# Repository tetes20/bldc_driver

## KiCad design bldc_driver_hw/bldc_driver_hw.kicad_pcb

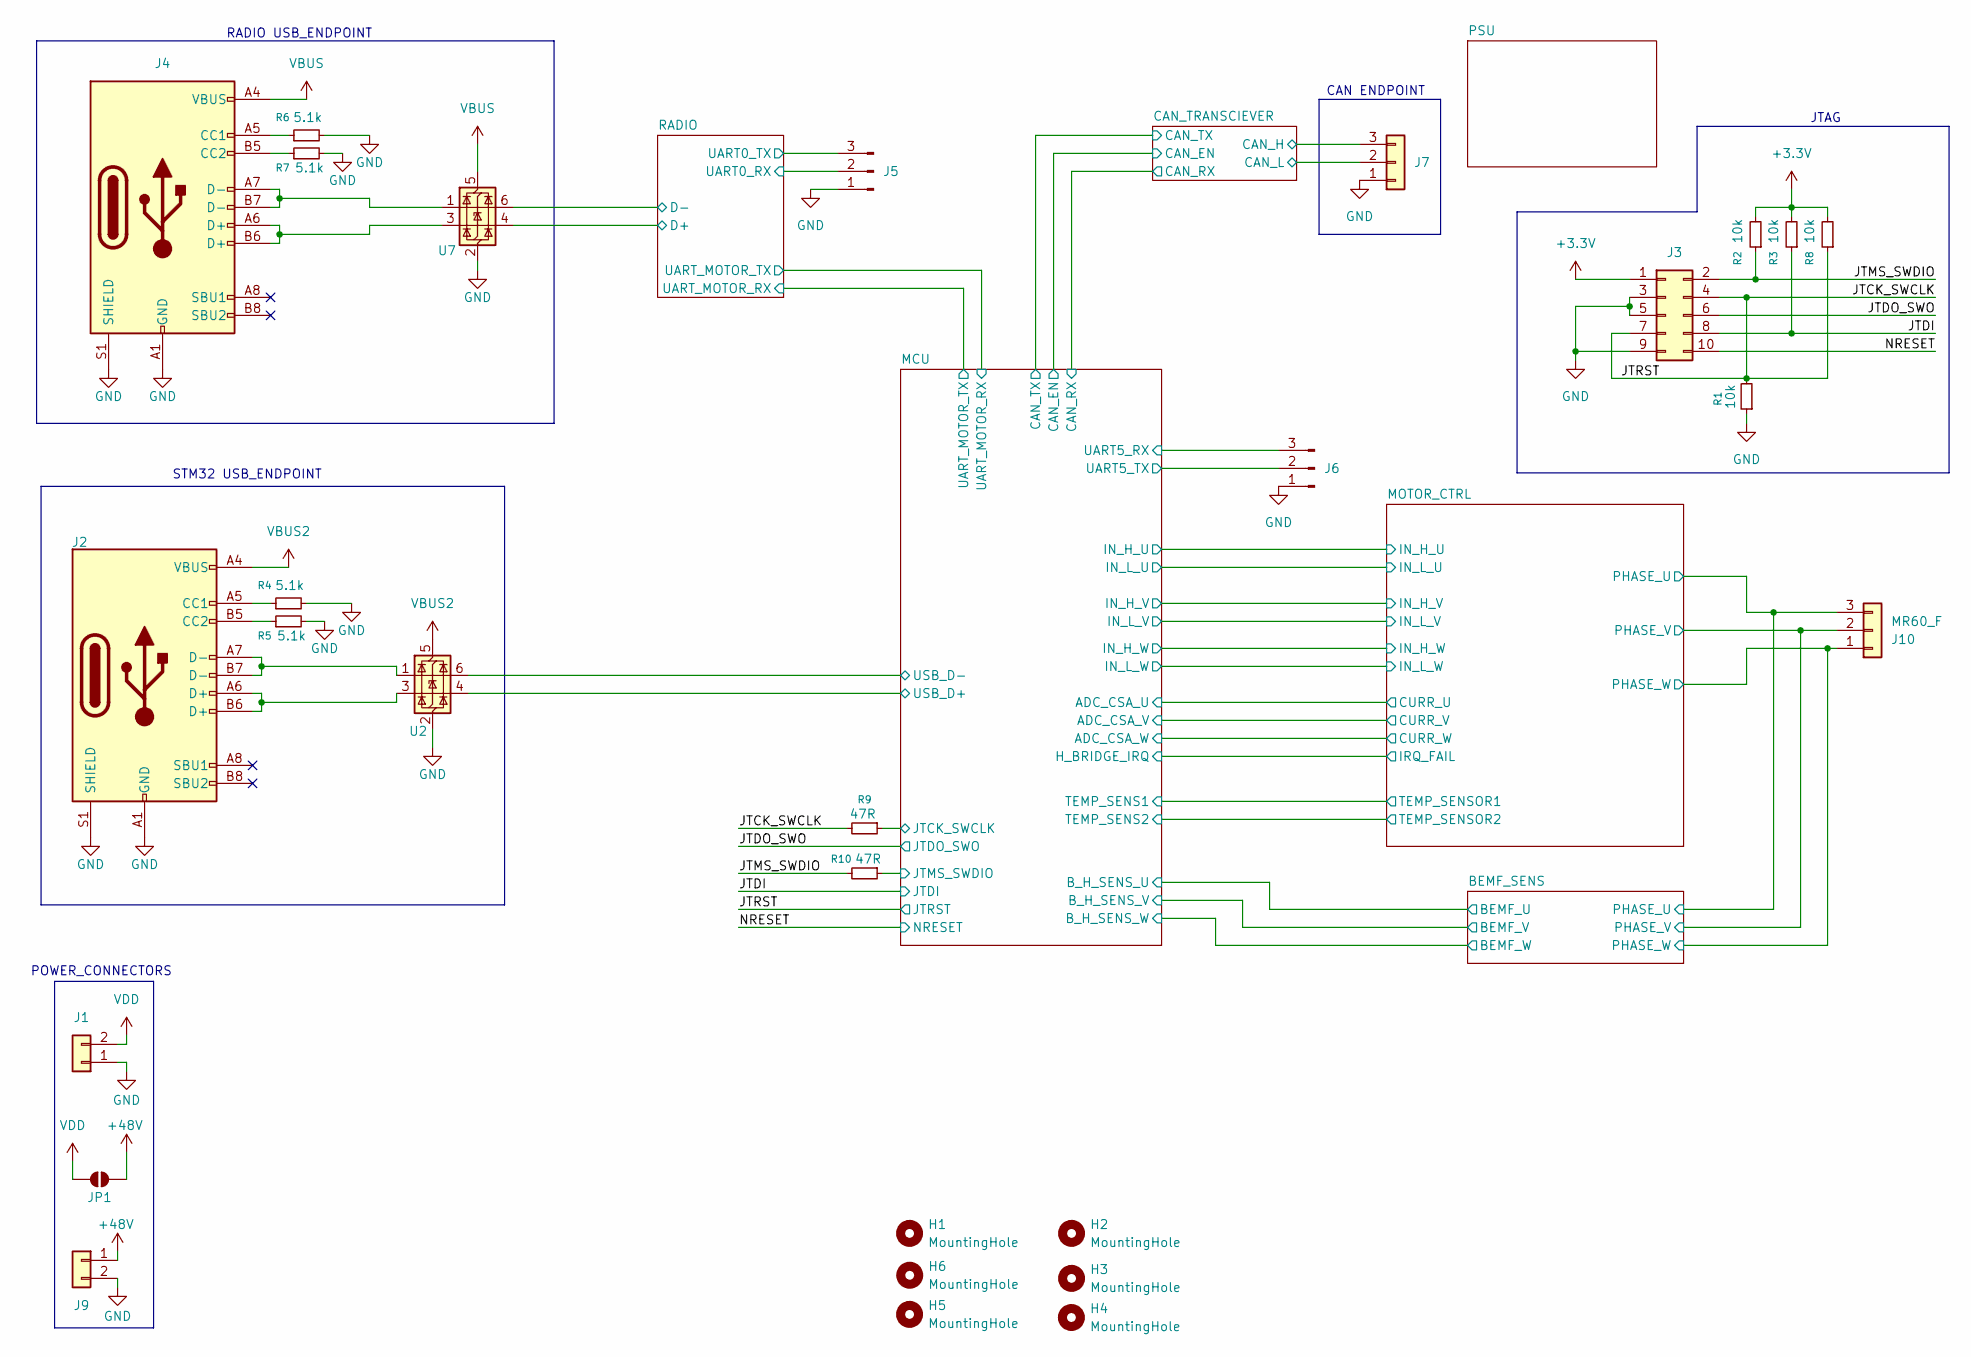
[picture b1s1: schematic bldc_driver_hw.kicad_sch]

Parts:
H1, H2, H3, H4, H5, H6: MountingHole; MountingHole_3.2mm_M3
J1: Conn_01x02; TerminalBlock_4Ucon_1x02_P3.50mm_Horizontal
J2, J4: USB_C_Receptacle_USB2.0_16P; USB_C_Receptacle_GCT_USB4105-xx-A_16P_TopMnt_Horizontal
J3: JTAG_CONN; PinHeader_2x05_P2.54mm_Vertical
J5, J6: Conn_01x03_Pin; PinHeader_1x03_P2.54mm_Vertical
J7: Conn_01x03; TerminalBlock_4Ucon_1x03_P3.50mm_Horizontal
J9: Conn_01x02; AMASS_XT60-F_1x02_P7.20mm_Vertical
J10: MR60_F; PhoenixContact_GMSTBVA_2,5_3-G_1x03_P7.50mm_Vertical
JP1: SolderJumper_2_Open; SolderJumper-2_P1.3mm_Open_Pad1.0x1.5mm
R1, R2, R3, R8: 10k; R_0603_1608Metric; LCSC C25804
R4, R5, R6, R7: 5.1k; R_0603_1608Metric; LCSC C23186
R9, R10: 47R; R_0603_1608Metric; LCSC C23182
U2, U7: USBLC6-2SC6; SOT-23-6

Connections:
+3.3V: J3.1, R2.2, R3.2, R8.2; also elsewhere on the board
+48V: J9.1, JP1.1 (A); also elsewhere on the board
/BEMF_SENS/PHASE_U: J10.3; also elsewhere on the board
/BEMF_SENS/PHASE_V: J10.2; also elsewhere on the board
/BEMF_SENS/PHASE_W: J10.1; also elsewhere on the board
/CAN_TRANSCIEVER/CAN_H: J7.3; also elsewhere on the board
/CAN_TRANSCIEVER/CAN_L: J7.2; also elsewhere on the board
/JTCK_SWCLK: J3.4, J3.7, R1.2, R8.1, R9.2; also elsewhere on the board
/JTDI: J3.8, R3.1; also elsewhere on the board
/JTDO_SWO: J3.6; also elsewhere on the board
/JTMS_SWDIO: J3.2, R2.1, R10.2
/MCU/JTCK_SWCLK: R9.1; also elsewhere on the board
/MCU/JTMS_SWDIO: R10.1; also elsewhere on the board
/MCU/UART5_RX: J6.3; also elsewhere on the board
/MCU/UART5_TX: J6.2; also elsewhere on the board
/MCU/USB_D+: U2.4 (I/O2); also elsewhere on the board
/MCU/USB_D-: U2.6 (I/O1); also elsewhere on the board
/NRESET: J3.10; also elsewhere on the board
/RADIO/D+: U7.4 (I/O2); also elsewhere on the board
/RADIO/D-: U7.6 (I/O1); also elsewhere on the board
/RADIO/UART0_RX: J5.2; also elsewhere on the board
/RADIO/UART0_TX: J5.3; also elsewhere on the board
GND: J1.1, J2.A1 (GND), J2.A12 (GND), J2.B1 (GND), J2.B12 (GND), J2.S1 (SHIELD), J3.3, J3.5, J3.9, J4.A1 (GND), J4.A12 (GND), J4.B1 (GND), J4.B12 (GND), J4.S1 (SHIELD), J5.1, J6.1, J7.1, J9.2, R1.1, R4.2, R5.2, R6.2, R7.2, U2.2 (GND), U7.2 (GND); also elsewhere on the board
unnamed: J2.A5 (CC1), R4.1
unnamed: J2.B5 (CC2), R5.1
unnamed: J2.A6 (D+), J2.B6 (D+), U2.3 (I/O2)
unnamed: J2.A7 (D-), J2.B7 (D-), U2.1 (I/O1)
unnamed: J4.A5 (CC1), R6.1
unnamed: J4.B5 (CC2), R7.1
unnamed: J4.A6 (D+), J4.B6 (D+), U7.3 (I/O2)
unnamed: J4.A7 (D-), J4.B7 (D-), U7.1 (I/O1)
VBUS: J4.A4 (VBUS), J4.A9 (VBUS), J4.B4 (VBUS), J4.B9 (VBUS), U7.5 (VBUS); also elsewhere on the board
VBUS2: J2.A4 (VBUS), J2.A9 (VBUS), J2.B4 (VBUS), J2.B9 (VBUS), U2.5 (VBUS); also elsewhere on the board
VDD: J1.2, JP1.2 (B); also elsewhere on the board

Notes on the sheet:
STM32 USB_ENDPOINT
JTAG
RADIO USB_ENDPOINT
CAN ENDPOINT
POWER_CONNECTORS

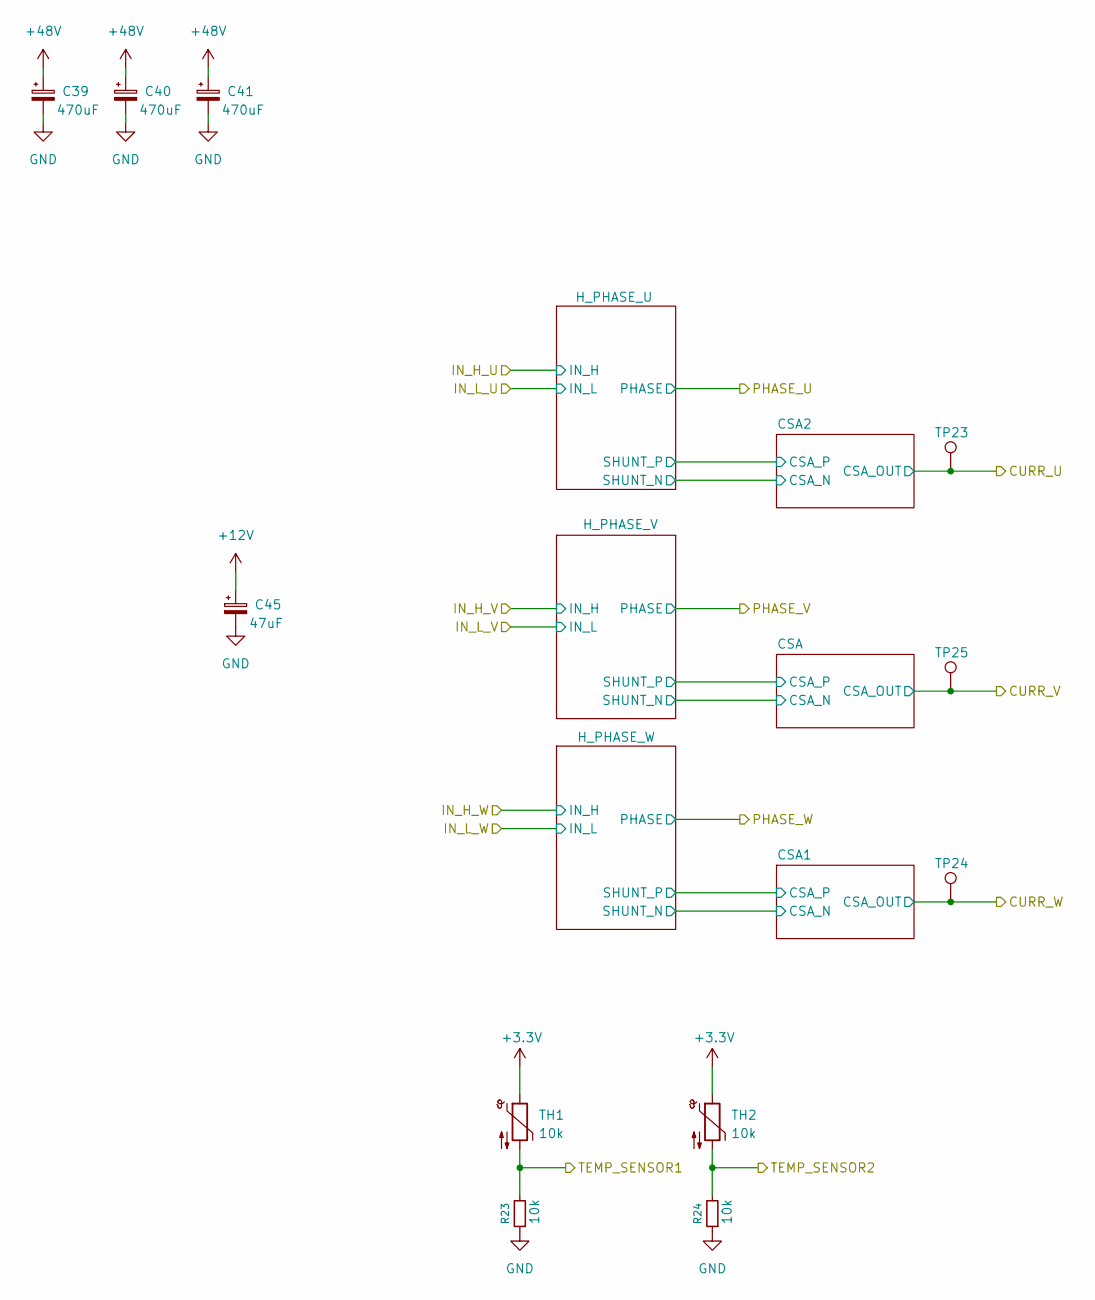
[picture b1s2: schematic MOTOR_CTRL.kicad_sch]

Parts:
C39, C40, C41: 470uF; CP_Radial_D16.0mm_P7.50mm
C45: 47uF; CP_Elec_6.3x5.4
R23, R24: 10k; R_0603_1608Metric; LCSC C25804
TH1, TH2: 10k; R_0603_1608Metric
TP23, TP24, TP25: TestPoint; TestPoint_Pad_D2.0mm

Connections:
+3.3V: TH1.1, TH2.1; also elsewhere on the board
+12V: C45.1; also elsewhere on the board
+48V: C39.1, C40.1, C41.1; also elsewhere on the board
/MCU/ADC_CSA_U: TP23.1; also elsewhere on the board
/MCU/ADC_CSA_V: TP25.1; also elsewhere on the board
/MCU/ADC_CSA_W: TP24.1; also elsewhere on the board
/MCU/TEMP_SENS1: R23.2, TH1.2; also elsewhere on the board
/MCU/TEMP_SENS2: R24.2, TH2.2; also elsewhere on the board
GND: C39.2, C40.2, C41.2, C45.2, R23.1, R24.1; also elsewhere on the board

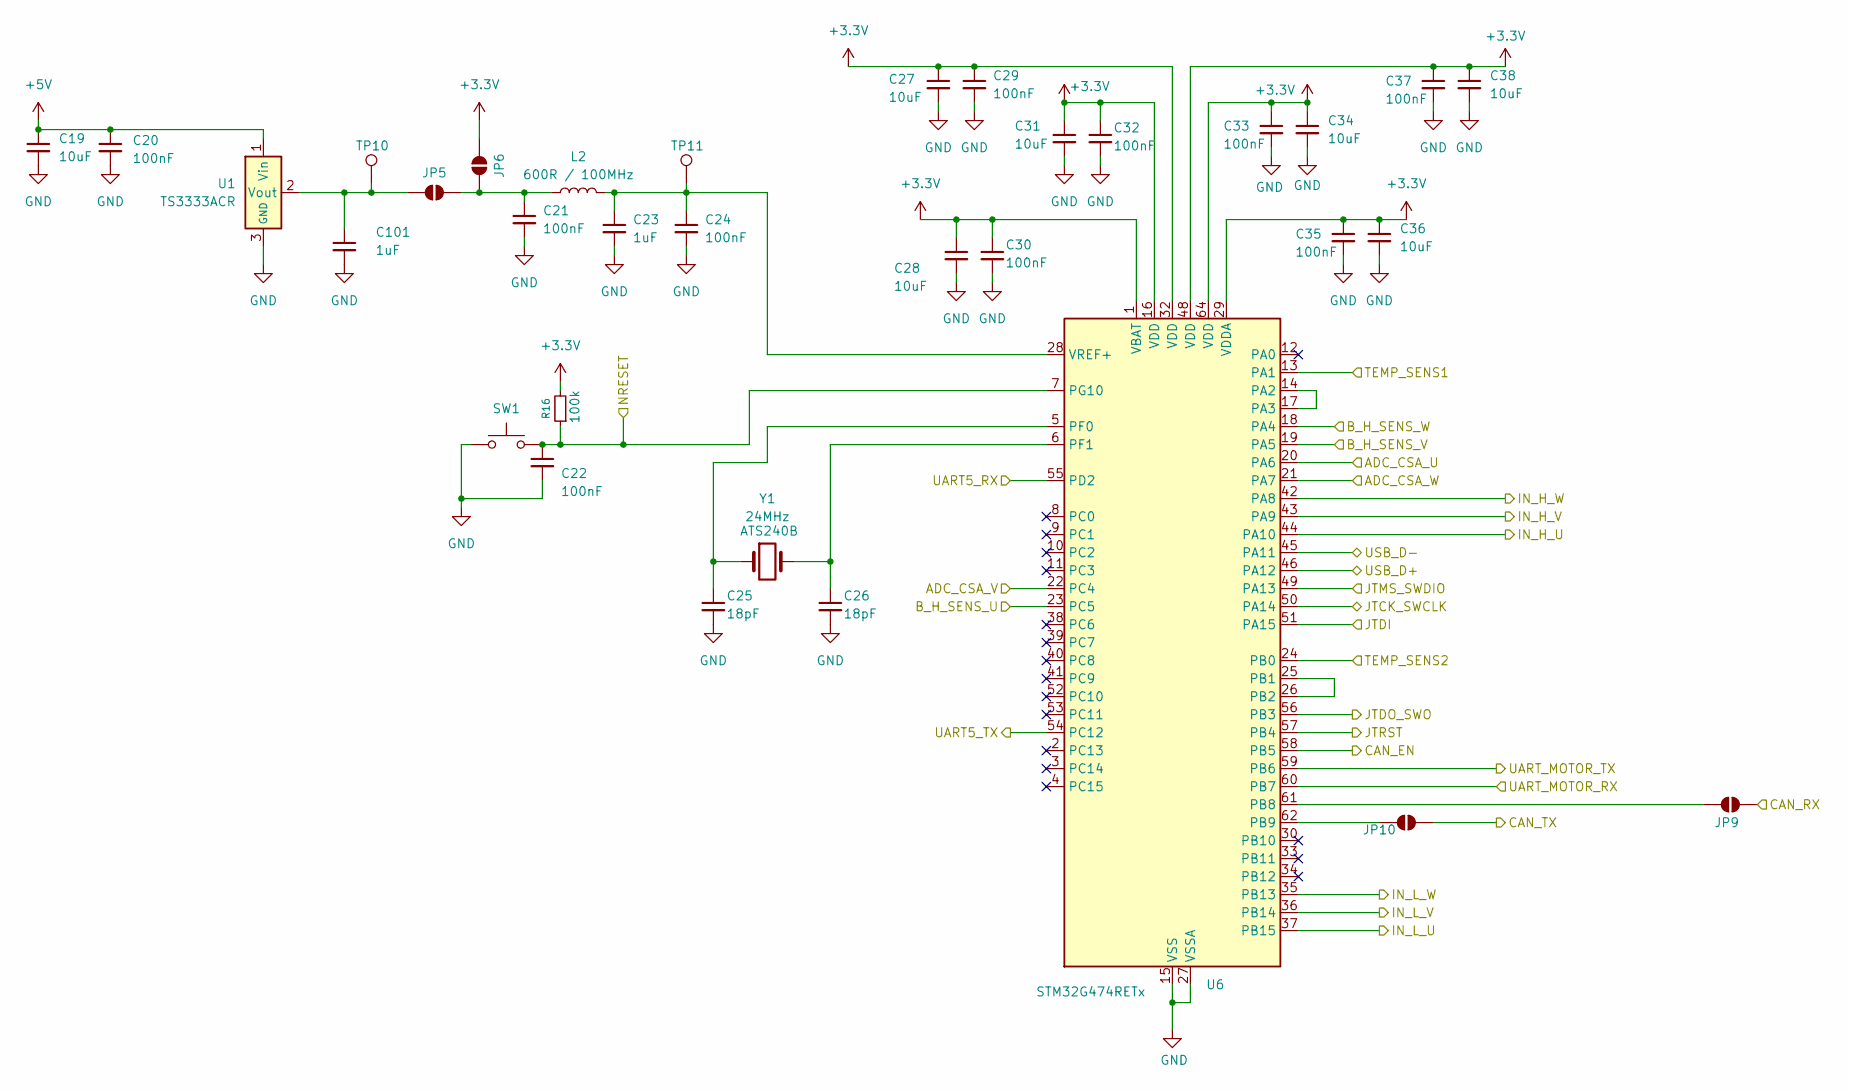
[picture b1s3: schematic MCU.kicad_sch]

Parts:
C19, C27, C28, C31, C34, C36, C38: 10uF; C_0603_1608Metric; LCSC C96446
C20, C21, C22, C24, C29, C30, C32, C33, C35, C37: 100nF; C_0603_1608Metric; LCSC C14663
C23, C101: 1uF; C_0603_1608Metric; LCSC C15849
C25, C26: 18pF; C_0603_1608Metric; LCSC C1647
JP5, JP6, JP9, JP10: SolderJumper_2_Open; SolderJumper-2_P1.3mm_Open_RoundedPad1.0x1.5mm
L2: 600R / 100MHz; R_1206_3216Metric
R16: 100k; R_0603_1608Metric; LCSC C25803
SW1: SW_Push; SW_SPST_TL3342; LCSC C318884
TP10, TP11: TestPoint; TestPoint_Pad_D2.0mm
U1: TS3333ACR; SOT-23-3
U6: STM32G474RETx; LQFP-64_10x10mm_P0.5mm
Y1: 24MHz; Crystal_HC49-U_Vertical

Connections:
+3.3V: C27.1, C28.1, C29.1, C30.1, C31.1, C32.1, C33.1, C34.1, C35.1, C36.1, C37.1, C38.1, JP6.1 (A), R16.2, U6.1 (VBAT), U6.16 (VDD), U6.29 (VDDA), U6.32 (VDD), U6.48 (VDD), U6.64 (VDD); also elsewhere on the board
+5V: C19.1, C20.1, U1.1 (Vin); also elsewhere on the board
/BEMF_SENS/BEMF_U: U6.23 (PC5); also elsewhere on the board
/BEMF_SENS/BEMF_V: U6.19 (PA5); also elsewhere on the board
/BEMF_SENS/BEMF_W: U6.18 (PA4); also elsewhere on the board
/CAN_TRANSCIEVER/CAN_EN: U6.58 (PB5); also elsewhere on the board
/CAN_TRANSCIEVER/CAN_RX: JP9.2 (B); also elsewhere on the board
/CAN_TRANSCIEVER/CAN_TX: JP10.2 (B); also elsewhere on the board
/JTCK_SWCLK: U6.57 (PB4); also elsewhere on the board
/JTDI: U6.51 (PA15); also elsewhere on the board
/JTDO_SWO: U6.56 (PB3); also elsewhere on the board
/MCU/ADC_CSA_U: U6.20 (PA6); also elsewhere on the board
/MCU/ADC_CSA_V: U6.22 (PC4); also elsewhere on the board
/MCU/ADC_CSA_W: U6.21 (PA7); also elsewhere on the board
/MCU/IN_H_U: U6.44 (PA10); also elsewhere on the board
/MCU/IN_H_V: U6.43 (PA9); also elsewhere on the board
/MCU/IN_H_W: U6.42 (PA8); also elsewhere on the board
/MCU/IN_L_U: U6.37 (PB15); also elsewhere on the board
/MCU/IN_L_V: U6.36 (PB14); also elsewhere on the board
/MCU/IN_L_W: U6.35 (PB13); also elsewhere on the board
/MCU/JTCK_SWCLK: U6.50 (PA14); also elsewhere on the board
/MCU/JTMS_SWDIO: U6.49 (PA13); also elsewhere on the board
/MCU/TEMP_SENS1: U6.13 (PA1); also elsewhere on the board
/MCU/TEMP_SENS2: U6.24 (PB0); also elsewhere on the board
/MCU/UART5_RX: U6.55 (PD2); also elsewhere on the board
/MCU/UART5_TX: U6.54 (PC12); also elsewhere on the board
/MCU/UART_MOTOR_RX: U6.60 (PB7); also elsewhere on the board
/MCU/UART_MOTOR_TX: U6.59 (PB6); also elsewhere on the board
/MCU/USB_D+: U6.46 (PA12); also elsewhere on the board
/MCU/USB_D-: U6.45 (PA11); also elsewhere on the board
/NRESET: C22.1, R16.1, SW1.2, U6.7 (PG10); also elsewhere on the board
GND: C19.2, C20.2, C21.2, C22.2, C23.2, C24.2, C25.2, C26.2, C27.2, C28.2, C29.2, C30.2, C31.2, C32.2, C33.2, C34.2, C35.2, C36.2, C37.2, C38.2, C101.2, SW1.1, U1.3 (GND), U6.15 (VSS), U6.27 (VSSA), U6.31 (VSS), U6.47 (VSS), U6.63 (VSS); also elsewhere on the board
unnamed: C101.1, JP5.1 (A), TP10.1, U1.2 (Vout)
unnamed: C21.1, JP5.2 (B), JP6.2 (B), L2.1
unnamed: JP9.1 (A), U6.61 (PB8)
unnamed: JP10.1 (A), U6.62 (PB9)
unnamed: U6.14 (PA2), U6.17 (PA3)
unnamed: U6.25 (PB1), U6.26 (PB2)
unnamed: C25.1, U6.5 (PF0), Y1.1
unnamed: C26.1, U6.6 (PF1), Y1.2
unnamed: C23.1, C24.1, L2.2, TP11.1, U6.28 (VREF+)

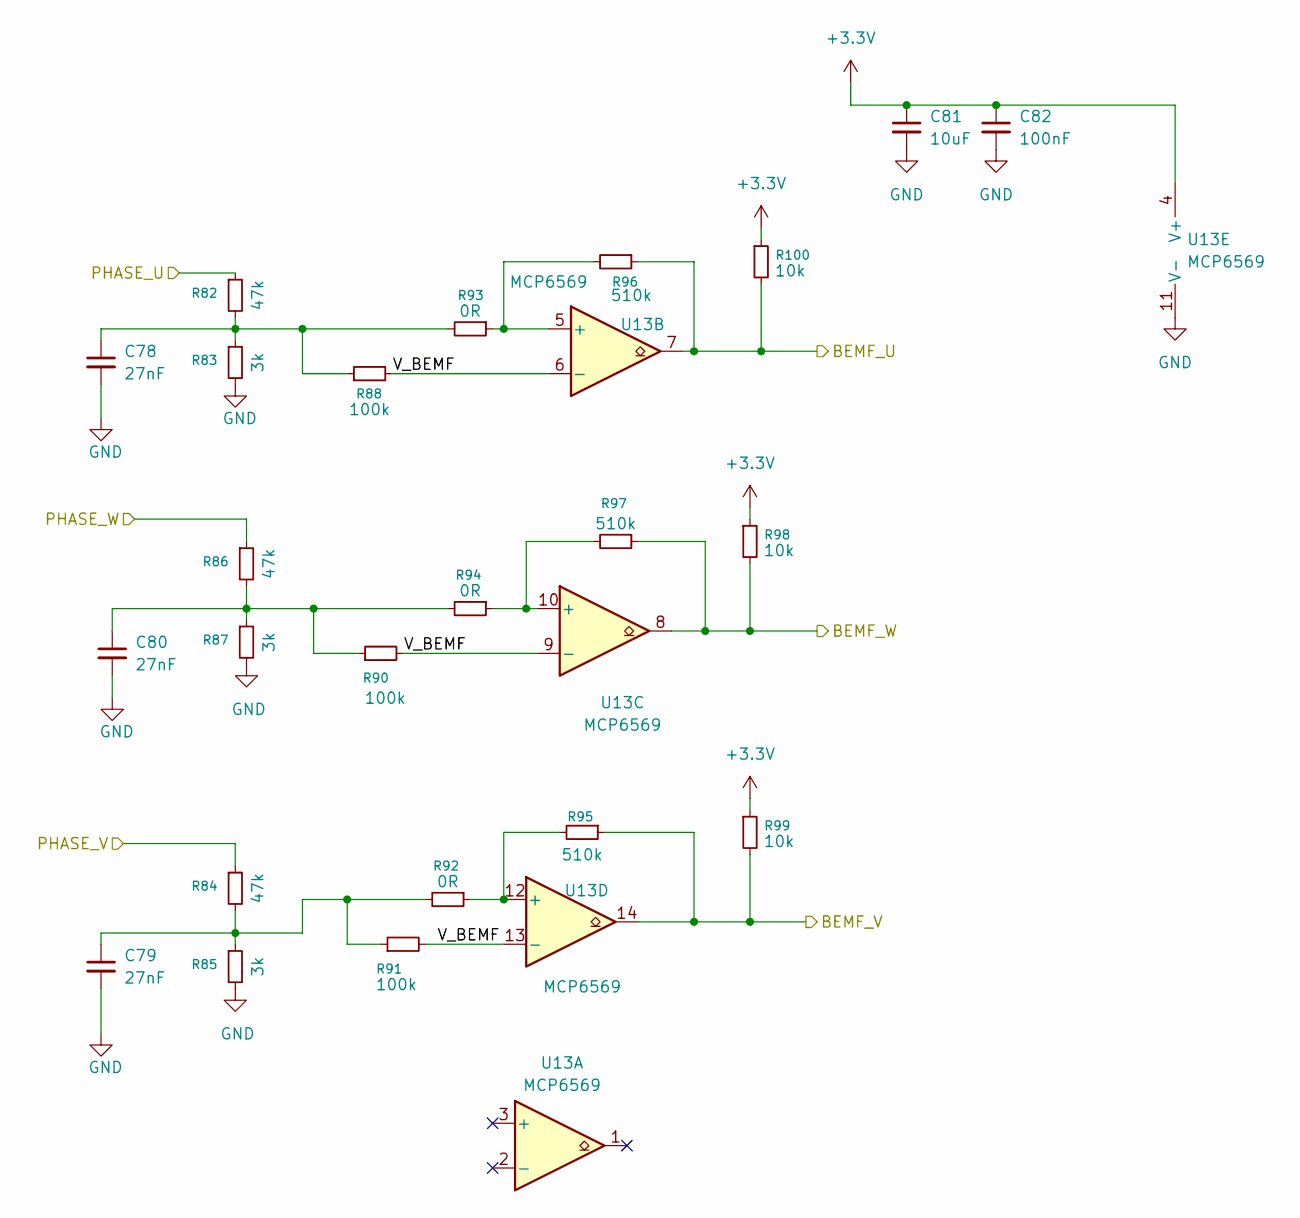
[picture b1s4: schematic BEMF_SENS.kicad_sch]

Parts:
C78, C79, C80: 27nF; C_0603_1608Metric
C81: 10uF; C_0603_1608Metric; LCSC C96446
C82: 100nF; C_0603_1608Metric; LCSC C14663
R82, R84, R86: 47k; R_0603_1608Metric; LCSC C25819
R83, R85, R87: 3k; R_0603_1608Metric; LCSC C4211
R88, R90, R91: 100k; R_0603_1608Metric; LCSC C25803
R92, R93, R94: 0R; R_0603_1608Metric; LCSC C21189
R95, R96, R97: 510k; R_0603_1608Metric; LCSC C23192
R98, R99, R100: 10k; R_0603_1608Metric; LCSC C25804
U13: MCP6569; SOIC-14_3.9x8.7mm_P1.27mm

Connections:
+3.3V: C81.1, C82.1, R98.1, R99.1, R100.1, U13.4 (V+); also elsewhere on the board
/BEMF_SENS/BEMF_U: R96.1, R100.2, U13.7; also elsewhere on the board
/BEMF_SENS/BEMF_V: R95.1, R99.2, U13.14; also elsewhere on the board
/BEMF_SENS/BEMF_W: R97.1, R98.2, U13.8; also elsewhere on the board
/BEMF_SENS/PHASE_U: R82.1; also elsewhere on the board
/BEMF_SENS/PHASE_V: R84.1; also elsewhere on the board
/BEMF_SENS/PHASE_W: R86.1; also elsewhere on the board
/BEMF_SENS/V_BEMF: R88.2, R90.2, R91.2, U13.6 (-), U13.9 (-), U13.13 (-)
GND: C78.2, C79.2, C80.2, C81.2, C82.2, R83.2, R85.2, R87.2, U13.11 (V-); also elsewhere on the board
unnamed: C78.1, R82.2, R83.1, R88.1, R93.2
unnamed: C79.1, R84.2, R85.1, R91.1, R92.2
unnamed: C80.1, R86.2, R87.1, R90.1, R94.2
unnamed: R93.1, R96.2, U13.5 (+)
unnamed: R94.1, R97.2, U13.10 (+)
unnamed: R92.1, R95.2, U13.12 (+)

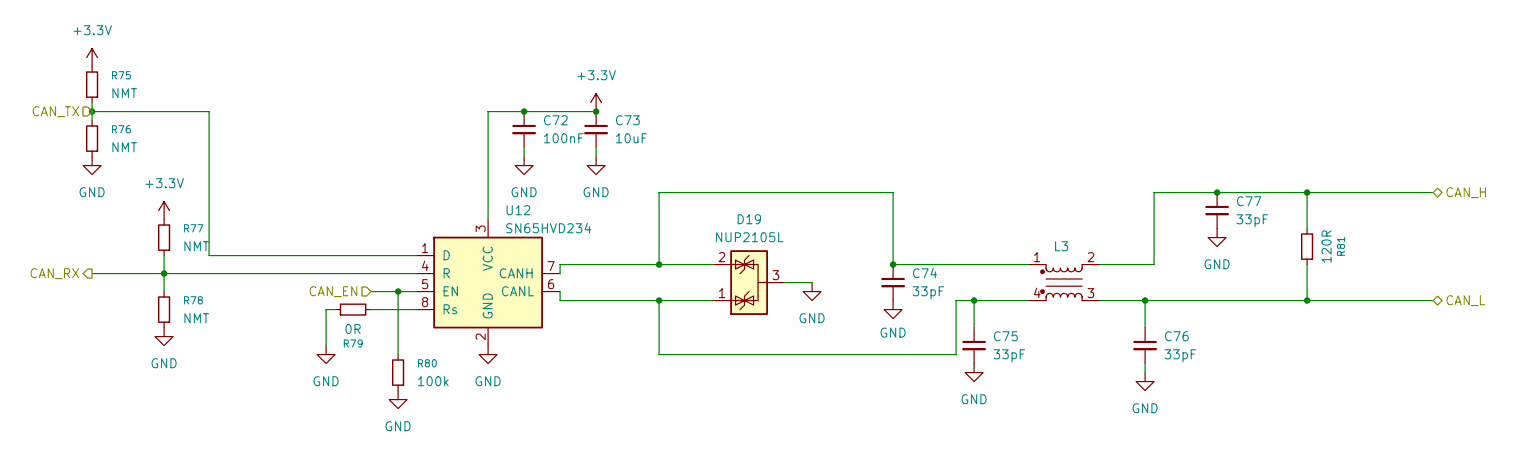
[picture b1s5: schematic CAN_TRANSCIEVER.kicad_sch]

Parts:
C72: 100nF; C_0603_1608Metric; LCSC C14663
C73: 10uF; C_0603_1608Metric; LCSC C96446
C74, C75, C76, C77: 33pF; C_0603_1608Metric; LCSC C1663
D19: NUP2105L; SOT-23
L3: Choke_Wurth_WE-CNSW_744232090; L_CommonMode_Wurth_WE-CNSW-1206
R75, R76, R77, R78: NMT; R_0603_1608Metric
R79: 0R; R_0603_1608Metric; LCSC C21189
R80: 100k; R_0603_1608Metric; LCSC C25803
R81: 120R; R_0603_1608Metric
U12: SN65HVD234; SOIC-8_3.9x4.9mm_P1.27mm

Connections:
+3.3V: C72.1, C73.1, R75.2, R77.2, U12.3 (VCC); also elsewhere on the board
/CAN_TRANSCIEVER/CAN_EN: R80.2, U12.5 (EN); also elsewhere on the board
/CAN_TRANSCIEVER/CAN_H: C77.1, L3.2, R81.2; also elsewhere on the board
/CAN_TRANSCIEVER/CAN_L: C76.1, L3.3, R81.1; also elsewhere on the board
/CAN_TRANSCIEVER/CAN_RX: R77.1, R78.2, U12.4 (R); also elsewhere on the board
/CAN_TRANSCIEVER/CAN_TX: R75.1, R76.2, U12.1 (D); also elsewhere on the board
GND: C72.2, C73.2, C74.2, C75.2, C76.2, C77.2, D19.3 (A), R76.1, R78.1, R79.1, R80.1, U12.2 (GND); also elsewhere on the board
unnamed: C74.1, D19.2 (K), L3.1, U12.7 (CANH)
unnamed: C75.1, D19.1 (K), L3.4, U12.6 (CANL)
unnamed: R79.2, U12.8 (Rs)

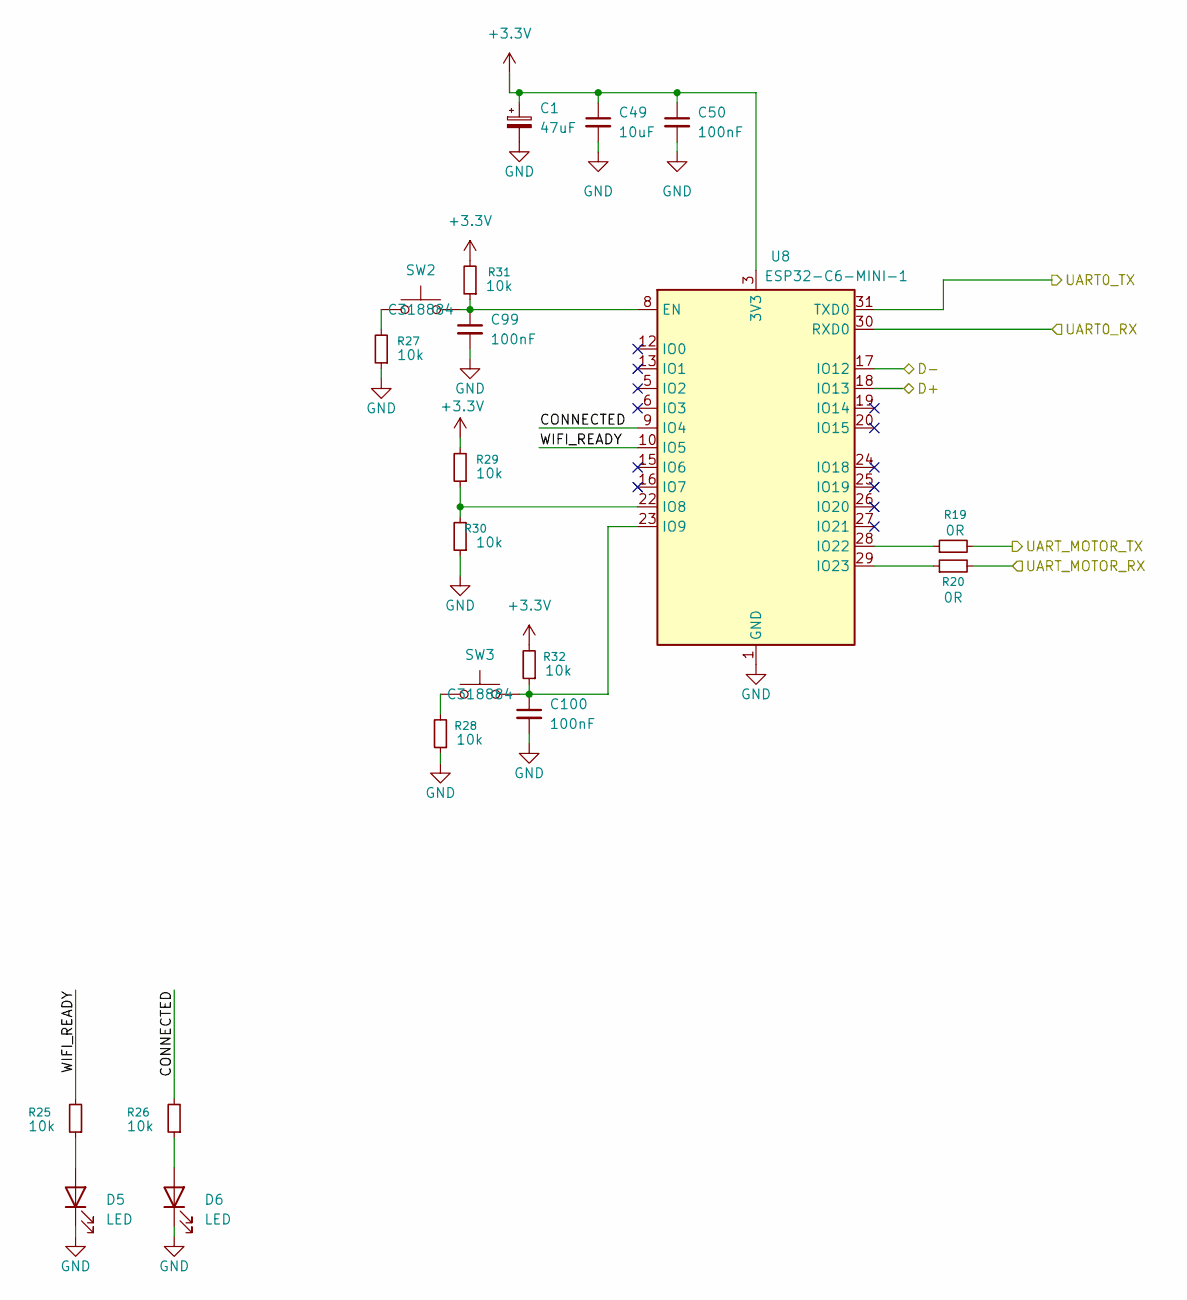
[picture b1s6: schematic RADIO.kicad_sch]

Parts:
C1: 47uF; CP_EIA-6032-15_Kemet-U
C49: 10uF; C_0603_1608Metric; LCSC C96446
C50, C99, C100: 100nF; C_0603_1608Metric; LCSC C14663
D5, D6: LED; LED_0603_1608Metric; LCSC C2286
R19, R20: 0R; R_0402_1005Metric; LCSC C17168
R25, R26, R27, R28, R29, R30, R31, R32: 10k; R_0603_1608Metric; LCSC C25804
SW2, SW3: SW_Push; SW_SPST_TL3342; LCSC C318884
U8: ESP32-C6-MINI-1; XCVR_ESP32-C6-MINI-1-H4

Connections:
+3.3V: C1.1, C49.1, C50.1, R29.2, R31.2, R32.2, U8.3 (3V3); also elsewhere on the board
/MCU/UART_MOTOR_RX: R19.2; also elsewhere on the board
/MCU/UART_MOTOR_TX: R20.2; also elsewhere on the board
/RADIO/CONNECTED: R26.2, U8.9 (IO4)
/RADIO/D+: U8.18 (IO13); also elsewhere on the board
/RADIO/D-: U8.17 (IO12); also elsewhere on the board
/RADIO/UART0_RX: U8.30 (RXD0); also elsewhere on the board
/RADIO/UART0_TX: U8.31 (TXD0); also elsewhere on the board
/RADIO/WIFI_READY: R25.2, U8.10 (IO5)
GND: C1.2, C49.2, C50.2, C99.2, C100.2, D5.1 (K), D6.1 (K), R27.1, R28.1, R30.1, U8.1 (GND), U8.2 (GND), U8.11 (GND), U8.14 (GND), U8.36 (GND), U8.37 (GND), U8.38 (GND), U8.39 (GND), U8.40 (GND), U8.41 (GND), U8.42 (GND), U8.43 (GND), U8.44 (GND), U8.45 (GND), U8.46 (GND), U8.47 (GND), U8.48 (GND), U8.49 (GND), U8.49_1 (GND), U8.49_2 (GND), U8.49_3 (GND), U8.49_4 (GND), U8.49_5 (GND), U8.49_6 (GND), U8.49_7 (GND), U8.49_8 (GND), U8.49_9 (GND), U8.50 (GND), U8.51 (GND), U8.52 (GND), U8.53 (GND); also elsewhere on the board
unnamed: D5.2 (A), R25.1
unnamed: D6.2 (A), R26.1
unnamed: R27.2, SW2.1
unnamed: R28.2, SW3.1
unnamed: C99.1, R31.1, SW2.2, U8.8 (EN)
unnamed: R29.1, R30.2, U8.22 (IO8)
unnamed: C100.1, R32.1, SW3.2, U8.23 (IO9)
unnamed: R19.1, U8.28 (IO22)
unnamed: R20.1, U8.29 (IO23)

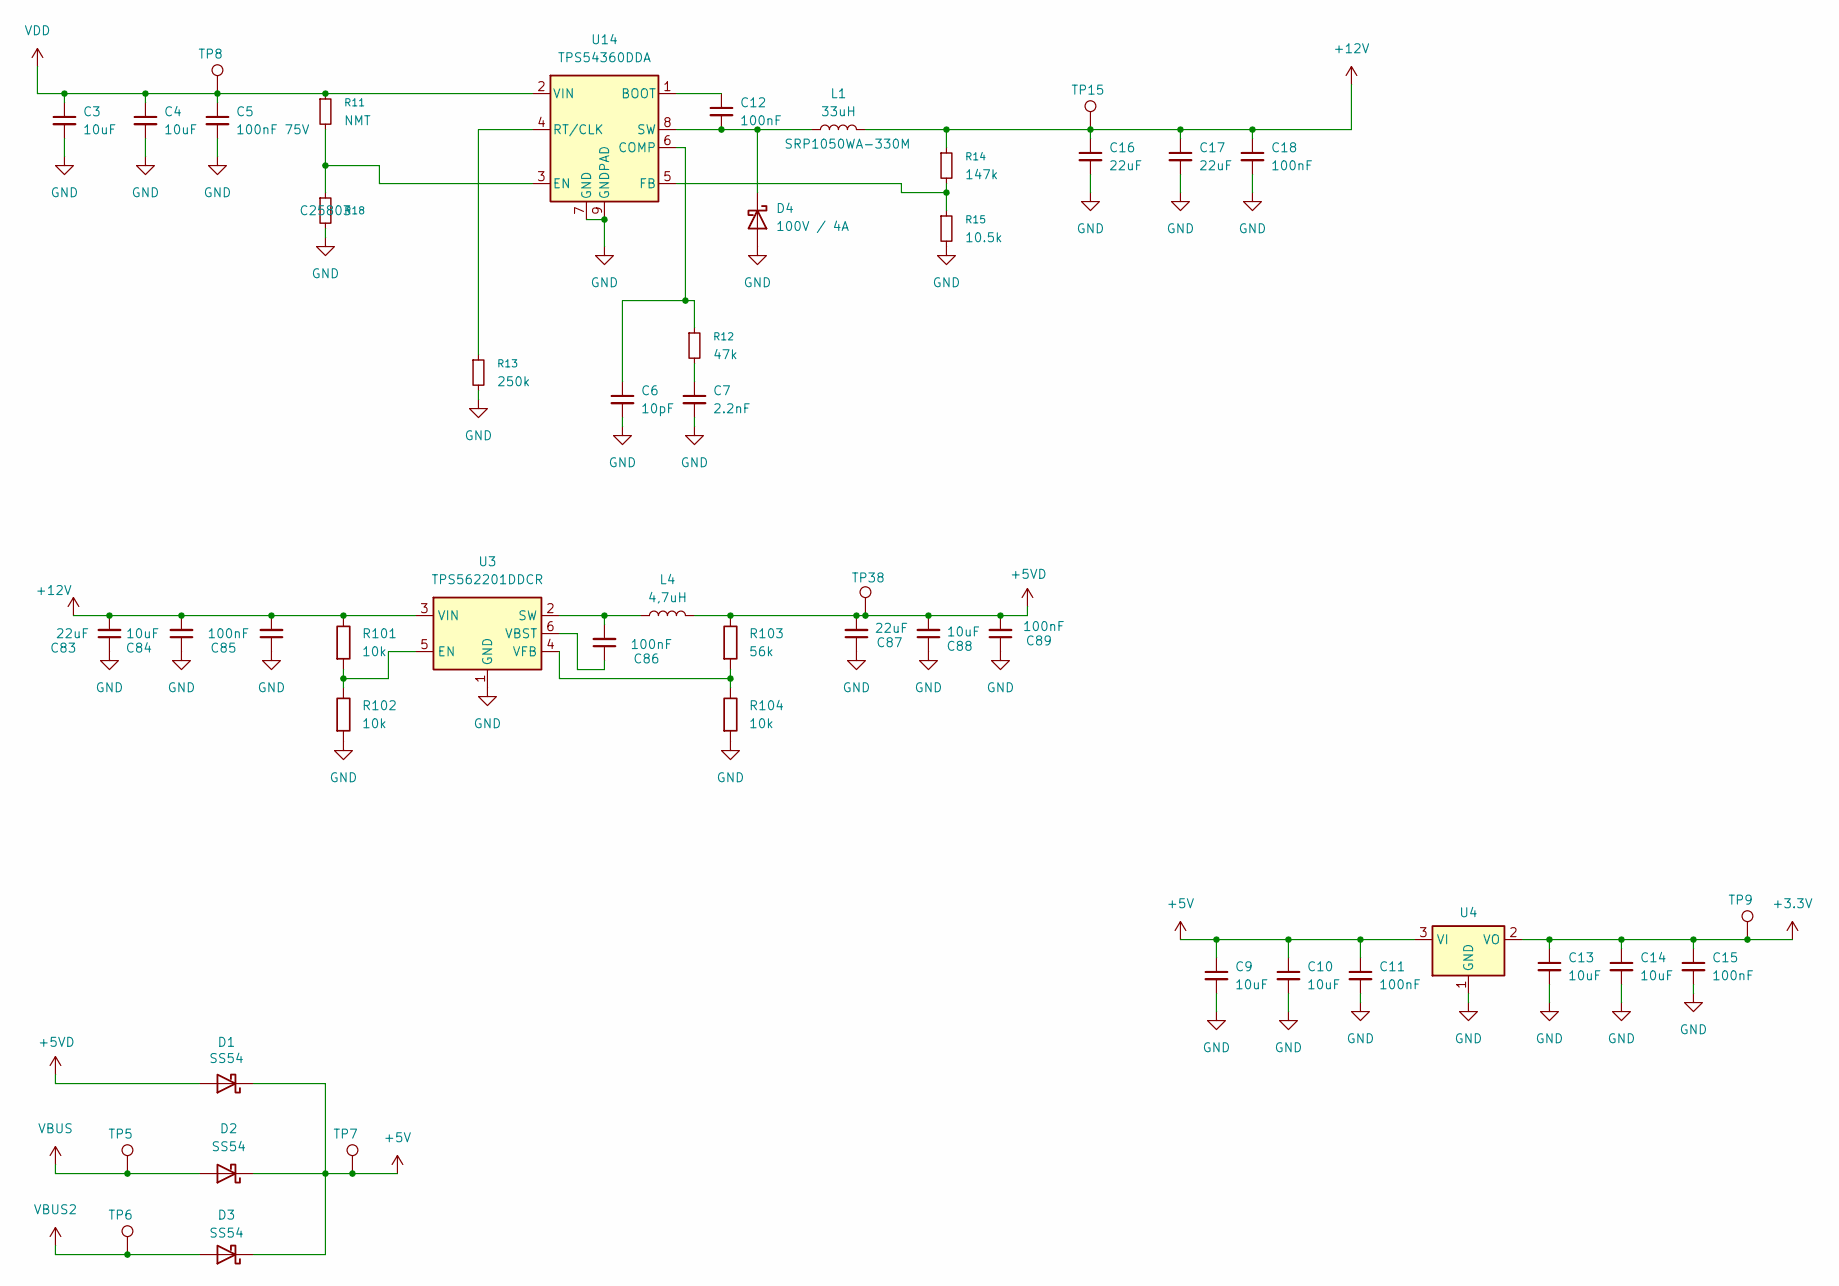
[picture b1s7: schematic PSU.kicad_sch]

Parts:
C3, C4: 10uF; C_1210_3225Metric
C5: 100nF 75V; C_0805_2012Metric; LCSC C28233
C6: 10pF; C_0603_1608Metric; LCSC C1634
C7: 2.2nF; C_0805_2012Metric; LCSC C28260
C9, C10, C13, C14, C84, C88: 10uF; C_0603_1608Metric; LCSC C96446
C11, C12, C15, C18, C85, C86, C89: 100nF; C_0603_1608Metric; LCSC C14663
C16, C17, C83, C87: 22uF; C_0805_2012Metric; LCSC C45783
D1, D2, D3: SS54; D_SMA; LCSC C22452
D4: 100V / 4A; D_SMB_Handsoldering
L1: 33uH; L_Bourns_SRP1050WA
L4: 4,7uH; INDPM5452X300N
R11: NMT; R_0603_1608Metric
R12: 47k; R_0603_1608Metric; LCSC C25819
R13: 250k; R_0603_1608Metric
R14: 147k; R_0603_1608Metric
R15: 10.5k; R_0603_1608Metric
R18: 100k; R_0603_1608Metric; LCSC C25803
R101, R102, R104: 10k; R_0603_1608Metric; LCSC C25804
R103: 56k; R_0603_1608Metric; LCSC C23206
TP5, TP6, TP7, TP8, TP9, TP15, TP38: TestPoint; TestPoint_Pad_D2.0mm
U3: TPS562201DDCR; SOT-23-6_Handsoldering
U4: AMS1117-3.3; SOT-223-3_TabPin2; LCSC C6186
U14: TPS54360DDA; TI_SO-PowerPAD-8_ThermalVias

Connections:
+3.3V: C13.1, C14.1, C15.1, TP9.1, U4.2 (VO); also elsewhere on the board
+5V: C9.1, C10.1, C11.1, D1.1 (K), D2.1 (K), D3.1 (K), TP7.1, U4.3 (VI); also elsewhere on the board
+5VD: C87.2, C88.2, C89.2, D1.2 (A), L4.2, R103.2, TP38.1
+12V: C16.1, C17.1, C18.1, C83.2, C84.2, C85.2, L1.2, R14.1, R101.2, TP15.1, U3.3 (VIN); also elsewhere on the board
GND: C3.2, C4.2, C5.2, C6.2, C7.2, C9.2, C10.2, C11.2, C13.2, C14.2, C15.2, C16.2, C17.2, C18.2, C83.1, C84.1, C85.1, C87.1, C88.1, C89.1, D4.2 (A), R13.2, R15.2, R18.2, R102.1, R104.1, U3.1 (GND), U4.1 (GND), U14.7 (GND), U14.9 (GNDPAD); also elsewhere on the board
unnamed: C7.1, R12.2
unnamed: C12.2, D4.1 (K), L1.1, U14.8 (SW)
unnamed: R101.1, R102.2, U3.5 (EN)
unnamed: C86.2, L4.1, U3.2 (SW)
unnamed: C86.1, U3.6 (VBST)
unnamed: R103.1, R104.2, U3.4 (VFB)
unnamed: C12.1, U14.1 (BOOT)
unnamed: C6.1, R12.1, U14.6 (COMP)
unnamed: R11.2, R18.1, U14.3 (EN)
unnamed: R14.2, R15.1, U14.5 (FB)
unnamed: R13.1, U14.4 (RT/CLK)
VBUS: D2.2 (A), TP5.1; also elsewhere on the board
VBUS2: D3.2 (A), TP6.1; also elsewhere on the board
VDD: C3.1, C4.1, C5.1, R11.1, TP8.1, U14.2 (VIN); also elsewhere on the board

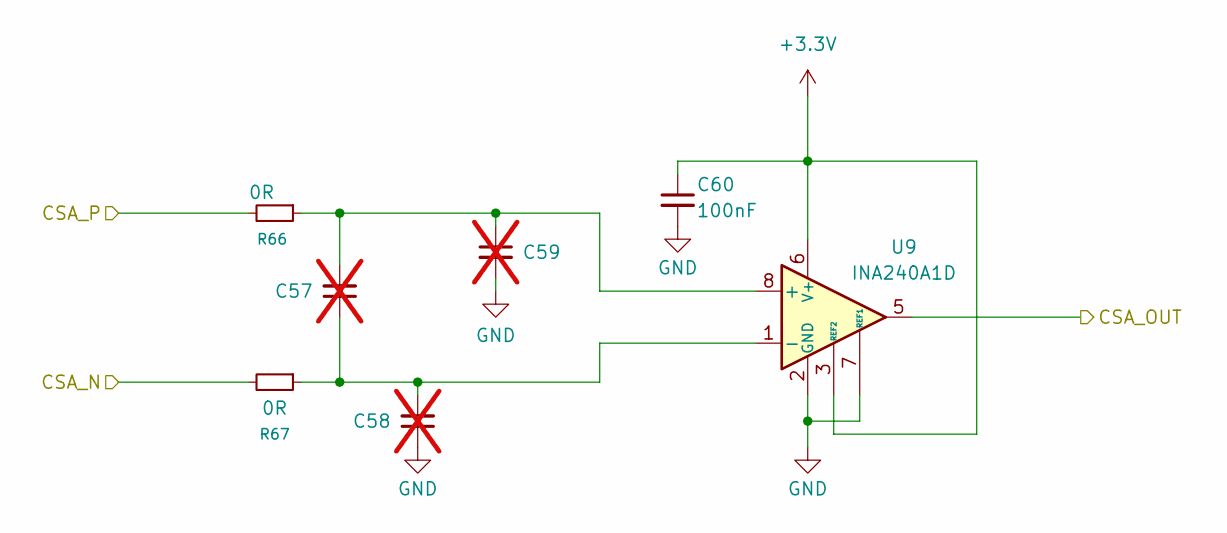
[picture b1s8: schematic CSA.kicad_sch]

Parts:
C57, C58, C59: C_Small; C_0603_1608Metric; not fitted
C60: 100nF; C_0603_1608Metric; LCSC C14663
R66, R67: 0R; R_0603_1608Metric; LCSC C21189
U9: INA240A1D; SOIC-8_3.9x4.9mm_P1.27mm

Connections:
+3.3V: C60.1, U9.3 (REF2), U9.6 (V+); also elsewhere on the board
/BEMF_SENS/PHASE_V: R67.2; also elsewhere on the board
/MCU/ADC_CSA_V: U9.5; also elsewhere on the board
/MOTOR_CTRL/CSA/CSA_P: R66.2; also elsewhere on the board
GND: C58.1, C59.2, C60.2, U9.2 (GND), U9.4 (GND), U9.7 (REF1); also elsewhere on the board
unnamed: C57.2, C59.1, R66.1, U9.8 (+)
unnamed: C57.1, C58.2, R67.1, U9.1 (-)

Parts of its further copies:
C61, C62, C63, C65, C66, C67: C_Small; C_0603_1608Metric; not fitted
C64, C68: 100nF; C_0603_1608Metric; LCSC C14663
R68, R69, R70, R71: 0R; R_0603_1608Metric; LCSC C21189
U10, U11: INA240A1D; SOIC-8_3.9x4.9mm_P1.27mm

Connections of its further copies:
+3.3V: C64.1, C68.1, U10.3 (REF2), U10.6 (V+), U11.3 (REF2), U11.6 (V+); also elsewhere on the board
/BEMF_SENS/PHASE_U: R71.2; also elsewhere on the board
/BEMF_SENS/PHASE_W: R69.2; also elsewhere on the board
/MCU/ADC_CSA_U: U11.5; also elsewhere on the board
/MCU/ADC_CSA_W: U10.5; also elsewhere on the board
/MOTOR_CTRL/CSA1/CSA_P: R68.2; also elsewhere on the board
/MOTOR_CTRL/CSA2/CSA_P: R70.2; also elsewhere on the board
GND: C62.1, C63.2, C64.2, C66.1, C67.2, C68.2, U10.2 (GND), U10.4 (GND), U10.7 (REF1), U11.2 (GND), U11.4 (GND), U11.7 (REF1); also elsewhere on the board
unnamed: C61.2, C63.1, R68.1, U10.8 (+)
unnamed: C61.1, C62.2, R69.1, U10.1 (-)
unnamed: C65.2, C67.1, R70.1, U11.8 (+)
unnamed: C65.1, C66.2, R71.1, U11.1 (-)
